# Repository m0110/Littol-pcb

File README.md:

# Littol-pcb
 scuffed pcb for littol

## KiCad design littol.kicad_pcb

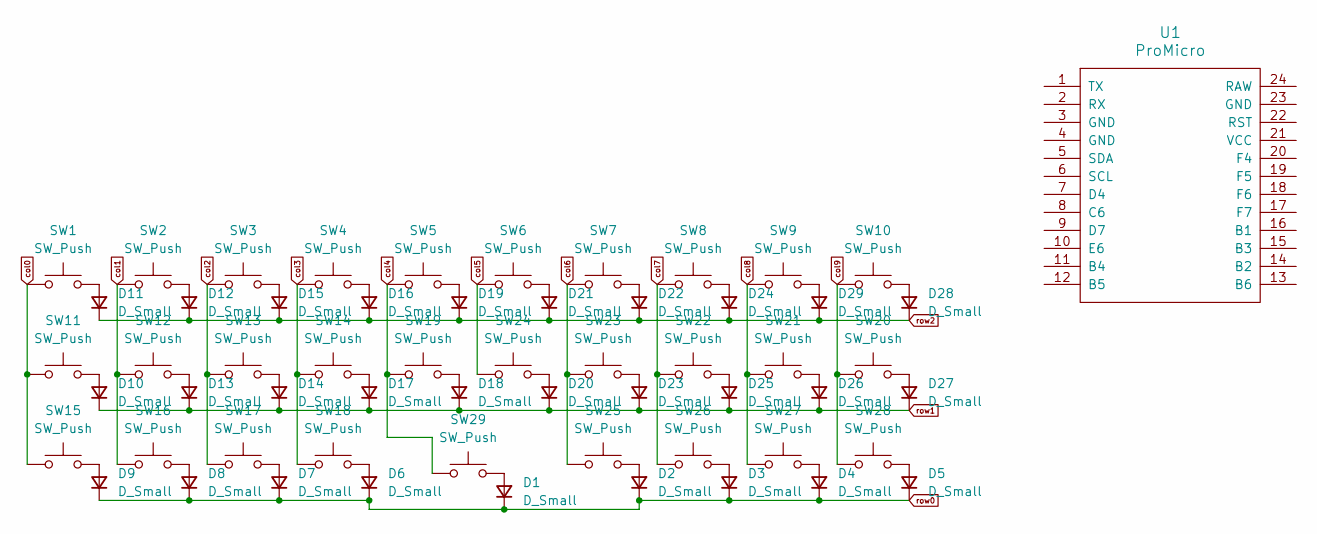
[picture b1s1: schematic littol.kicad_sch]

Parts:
D1, D2, D3, D4, D5, D6, D7, D8, D9, D10, D11, D12, D13, D14, D15, D16, D17, D18, D19, D20, D21, D22, D23, D24, D25, D26, D27, D28, D29: D_Small; D_SOD-123
SW1, SW10: SW_Push; Alps-Solderable-1.5U
SW2, SW3, SW4, SW5, SW6, SW7, SW8, SW9, SW12, SW13, SW14, SW15, SW16, SW17, SW18, SW19, SW21, SW22, SW23, SW24, SW25, SW26, SW27, SW28: SW_Push; Alps-Solderable-1U
SW11, SW20: SW_Push; Alps-Solderable-1.25U
SW29: SW_Push; Alps-Solderable-2U
U1: ProMicro

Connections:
unnamed: D1.2 (A), SW29.1
unnamed: D2.2 (A), SW25.1
unnamed: D3.2 (A), SW26.1
unnamed: D4.2 (A), SW27.1
unnamed: D5.2 (A), SW28.1
unnamed: D6.2 (A), SW18.1
unnamed: D7.2 (A), SW17.1
unnamed: D8.2 (A), SW16.1
unnamed: D9.2 (A), SW15.1
unnamed: D10.2 (A), SW11.1
unnamed: D11.2 (A), SW1.1
unnamed: D12.2 (A), SW2.1
unnamed: D13.2 (A), SW12.1
unnamed: D14.2 (A), SW13.1
unnamed: D15.2 (A), SW3.1
unnamed: D16.2 (A), SW4.1
unnamed: D17.2 (A), SW14.1
unnamed: D18.2 (A), SW19.1
unnamed: D19.2 (A), SW5.1
unnamed: D20.2 (A), SW24.1
unnamed: D21.2 (A), SW6.1
unnamed: D22.2 (A), SW7.1
unnamed: D23.2 (A), SW23.1
unnamed: D24.2 (A), SW8.1
unnamed: D25.2 (A), SW22.1
unnamed: D26.2 (A), SW21.1
unnamed: D27.2 (A), SW20.1
unnamed: D28.2 (A), SW10.1
unnamed: D29.2 (A), SW9.1
col0: SW1.2, SW11.2, SW15.2
col1: SW2.2, SW12.2, SW16.2
col2: SW3.2, SW13.2, SW17.2
col3: SW4.2, SW14.2, SW18.2
col4: SW5.2, SW19.2, SW29.2
col5: SW6.2, SW24.2
col6: SW7.2, SW23.2, SW25.2
col7: SW8.2, SW22.2, SW26.2
col8: SW9.2, SW21.2, SW27.2
col9: SW10.2, SW20.2, SW28.2
row0: D1.1 (K), D2.1 (K), D3.1 (K), D4.1 (K), D5.1 (K), D6.1 (K), D7.1 (K), D8.1 (K), D9.1 (K)
row1: D10.1 (K), D13.1 (K), D14.1 (K), D17.1 (K), D18.1 (K), D20.1 (K), D23.1 (K), D25.1 (K), D26.1 (K), D27.1 (K)
row2: D11.1 (K), D12.1 (K), D15.1 (K), D16.1 (K), D19.1 (K), D21.1 (K), D22.1 (K), D24.1 (K), D28.1 (K), D29.1 (K)

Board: 2 copper layers, 59 parts (0 on the bottom side), 42 nets, no tracks yet.

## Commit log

2023-07-08 made file
    mhm
2023-07-08 Add submodules
2023-07-09 made switches on schema
2023-07-09 added por micron
2023-07-09 started pcb
